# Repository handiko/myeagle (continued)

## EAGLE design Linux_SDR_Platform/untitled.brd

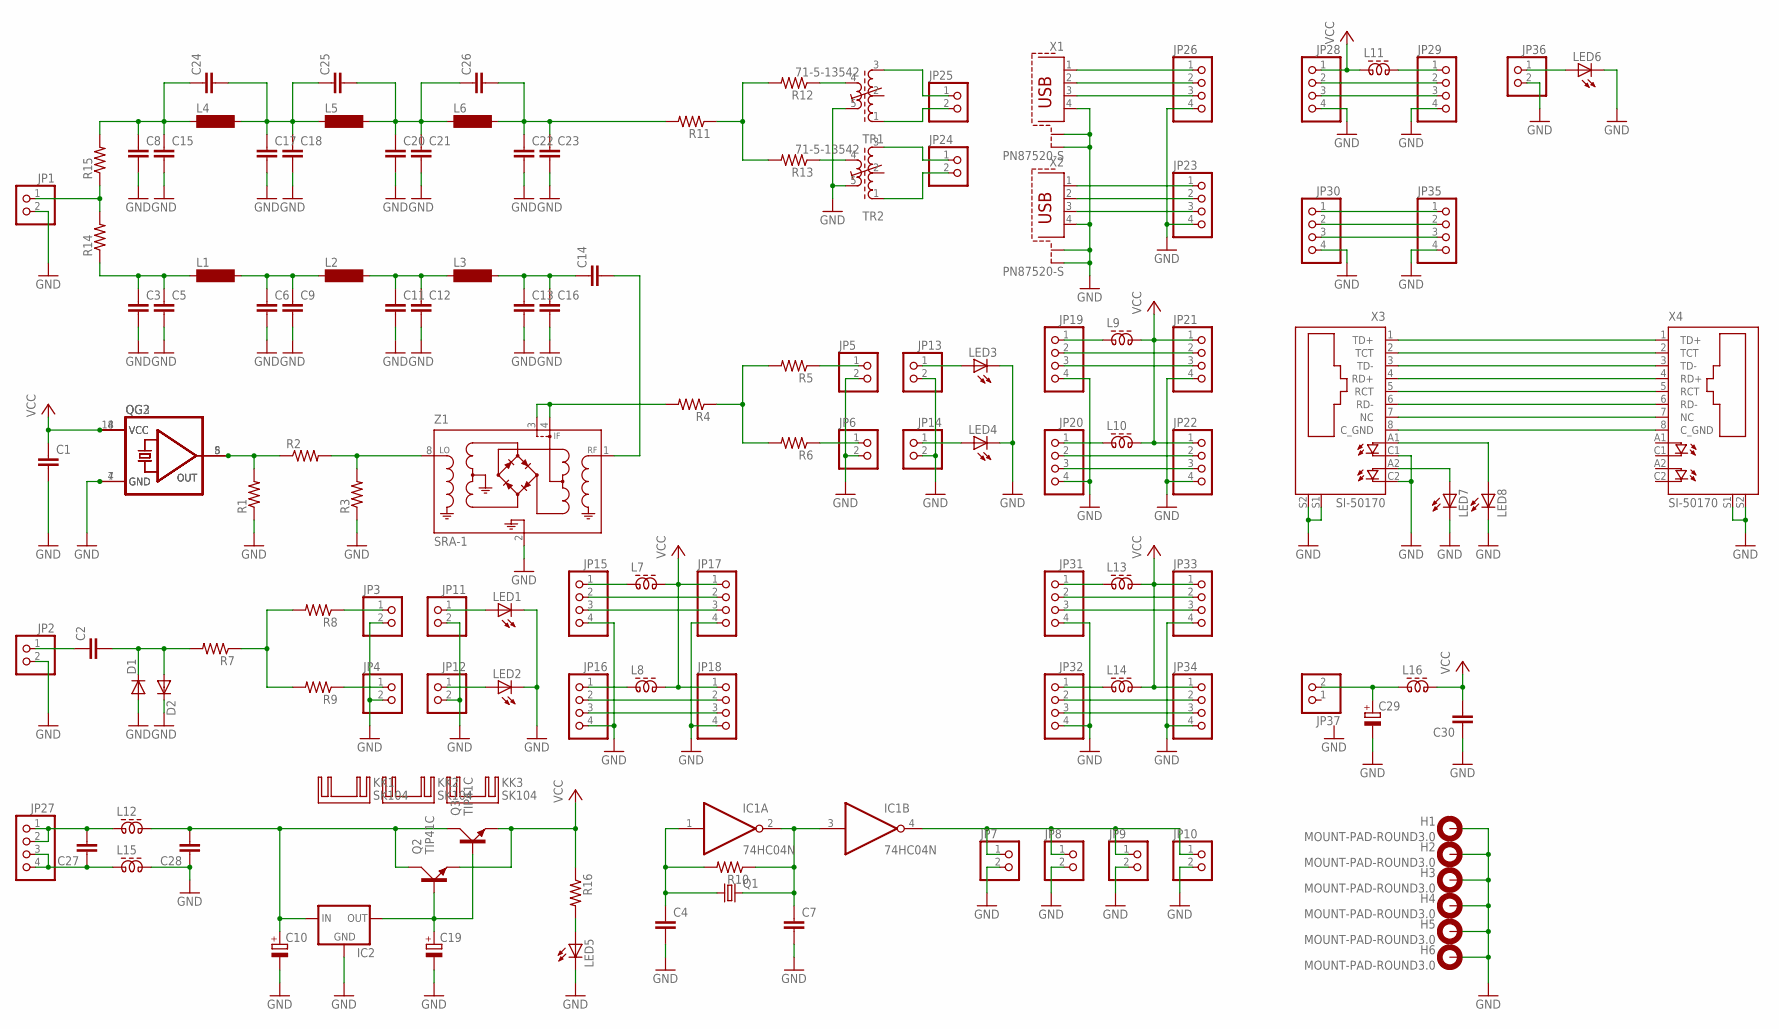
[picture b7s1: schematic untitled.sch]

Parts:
C1, C2, C3, C4, C5, C6, C7, C8, C9, C11, C12, C13, C14, C15, C16, C17, C18, C20, C21, C22, C23, C24, C25, C26, C27, C28, C30: C-EUC1206; C1206
C10, C19, C29: CPOL-EUE2.5-7; E2,5-7
D1, D2: DIODE-DO214AC; DO214AC
H1, H2, H3, H4, H5, H6: MOUNT-PAD-ROUND3.0; 3,0-PAD
IC1: 74HC04N; DIL14
IC2: 78XXS
JP1, JP2, JP3, JP4, JP5, JP6, JP7, JP8, JP9, JP10, JP11, JP12, JP13, JP14, JP24, JP25, JP36, JP37: PINHD-1X2; 1X02
JP15, JP16, JP17, JP18, JP19, JP20, JP21, JP22, JP23, JP26, JP27, JP28, JP29, JP30, JP31, JP32, JP33, JP34, JP35: PINHD-1X4; 1X04
KK1, KK2, KK3: SK104
L1, L2, L3, L4, L5, L6: BS75
L7, L8, L9, L10, L11, L12, L13, L14, L15, L16: ZD60820512; ZD6-2W5
LED1, LED2, LED3, LED4, LED5, LED6, LED7, LED8: LED3MM
Q1: CRYSTALHC49S; HC49/S
Q2, Q3: TIP41C; TO220AV
QG2: QG5460; DIL08S
QG3: QG5860; DIL14S
R1, R2, R3, R4, R5, R6, R7, R8, R9, R10, R11, R12, R13, R14, R15, R16: R-US_M1206; M1206
TR1, TR2: 71-5-13542; 71-5
X1, X2: PN87520-S
X3, X4: SI-50170
Z1: SRA-1; A01

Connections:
GND: C1.2, C3.2, C4.2, C5.2, C6.2, C7.2, C8.2, C9.2, C10.-, C11.2, C12.2, C13.2, C15.2, C16.2, C17.2, C18.2, C19.-, C20.2, C21.2, C22.2, C23.2, C28.1, C29.-, C30.1, D1.A, D2.C, H1.B3,0, H2.B3,0, H3.B3,0, H4.B3,0, H5.B3,0, H6.B3,0, IC1.7 (GND), IC2.GND, JP1.2, JP2.2, JP3.2, JP4.2, JP5.2, JP6.2, JP7.2, JP8.2, JP9.2, JP10.2, JP11.2, JP12.2, JP13.2, JP14.2, JP15.4, JP16.4, JP17.4, JP18.4, JP19.4, JP20.4, JP21.4, JP22.4, JP23.4, JP26.4, JP28.4, JP29.4, JP30.4, JP31.4, JP32.4, JP33.4, JP34.4, JP35.4, JP36.2, L15.2, LED1.K (C), LED2.K (C), LED3.K (C), LED4.K (C), LED5.K (C), LED6.K (C), LED7.K (C), LED8.K (C), QG2.4 (GND), QG3.7 (GND), R1.1, R3.1, TR1.5 (A2), TR2.5 (A2), X1.4, X1.S1, X1.S2, X2.4, X2.S1, X2.S2, X3.C1 (C), X3.C2 (C1), X3.S1, X3.S2, X4.S1, X4.S2, Z1.2 (CASEGROUND), Z1.5 (GND), Z1.6 (GND), Z1.7 (GND)
unnamed: C3.1, C5.1, L1.1, R14.1
unnamed: C6.1, C9.1, L1.2, L2.1
unnamed: JP1.1, R14.2, R15.1
unnamed: C11.1, C12.1, L2.2, L3.1
unnamed: C13.1, C14.1, C16.1, L3.2
unnamed: QG2.5 (OUT), QG3.8 (OUT), R1.2, R2.1
unnamed: R2.2, R3.2, Z1.8 (L)
unnamed: R4.2, Z1.3 (IF), Z1.4 (IF)
unnamed: C14.2, Z1.1 (R)
unnamed: R4.1, R5.2, R6.2
unnamed: C4.1, IC1.1 (I), Q1.1, R10.2
unnamed: C2.1, JP2.1
unnamed: C2.2, D1.C, D2.A, R7.2
unnamed: R7.1, R8.2, R9.2
unnamed: JP3.1, R8.1
unnamed: JP4.1, R9.1
unnamed: JP5.1, R5.1
unnamed: JP6.1, R6.1
unnamed: C7.1, IC1.2 (O), IC1.3 (I), Q1.2, R10.1
unnamed: IC1.4 (O), JP7.1, JP8.1, JP9.1, JP10.1
unnamed: JP11.1, LED1.A
unnamed: JP12.1, LED2.A
unnamed: JP13.1, LED3.A
unnamed: JP14.1, LED4.A
unnamed: JP15.2, JP17.2
unnamed: JP15.3, JP17.3
unnamed: JP16.2, JP18.2
unnamed: JP16.3, JP18.3
unnamed: JP15.1, L7.1
unnamed: JP16.1, L8.1
unnamed: JP19.2, JP21.2
unnamed: JP19.3, JP21.3
unnamed: C8.1, C15.1, C24.1, L4.1, R15.2
unnamed: C17.1, C18.1, C24.2, C25.1, L4.2, L5.1
unnamed: JP20.2, JP22.2
unnamed: C20.1, C21.1, C25.2, C26.1, L5.2, L6.1
unnamed: C22.1, C23.1, C26.2, L6.2, R11.2
unnamed: R13.1, TR2.4 (E2)
unnamed: R11.1, R12.2, R13.2
unnamed: R12.1, TR1.4 (E2)
unnamed: JP25.2, TR1.1 (A1)
unnamed: JP24.1, TR2.3 (E1)
unnamed: JP24.2, TR2.1 (A1)
unnamed: JP25.1, TR1.3 (E1)
unnamed: JP20.3, JP22.3
unnamed: JP19.1, L9.1
unnamed: JP20.1, L10.1
unnamed: JP26.1, X1.1
unnamed: JP26.2, X1.2
unnamed: JP26.3, X1.3
unnamed: JP23.1, X2.1
unnamed: JP23.2, X2.2
unnamed: JP23.3, X2.3
unnamed: C10.+, C28.2, IC2.IN, L12.2, Q2.C, Q3.C
unnamed: C19.+, IC2.OUT, Q2.B, Q3.B
unnamed: JP28.2, JP29.2
unnamed: JP28.3, JP29.3
unnamed: LED5.A, R16.2
unnamed: JP30.2, JP35.2
unnamed: JP31.2, JP33.2
unnamed: JP31.3, JP33.3
unnamed: JP32.2, JP34.2
unnamed: JP32.3, JP34.3
unnamed: JP31.1, L13.1
unnamed: JP32.1, L14.1
unnamed: JP29.1, L11.2
unnamed: JP30.3, JP35.3
unnamed: JP30.1, JP35.1
unnamed: JP36.1, LED6.A
unnamed: X3.1 (TD+), X4.1 (TD+)
unnamed: X3.2 (TCT), X4.2 (TCT)
unnamed: X3.3 (TD-), X4.3 (TD-)
unnamed: X3.4 (RD+), X4.4 (RD+)
unnamed: X3.5 (RCT), X4.5 (RCT)
unnamed: X3.6 (RD-), X4.6 (RD-)
unnamed: X3.7 (NC), X4.7 (NC)
unnamed: X3.8 (C_GND), X4.8 (C_GND)
unnamed: LED7.A, X3.A2 (A1)
unnamed: LED8.A, X3.A1 (A)
unnamed: C27.2, JP27.1, JP27.2, L12.1
unnamed: C27.1, JP27.3, JP27.4, L15.1
unnamed: C29.+, JP37.2, L16.1
VCC: C1.1, C30.2, IC1.14 (VCC), JP17.1, JP18.1, JP21.1, JP22.1, JP28.1, JP33.1, JP34.1, L7.2, L8.2, L9.2, L10.2, L11.1, L13.2, L14.2, L16.2, Q2.E, Q3.E, QG2.8 (VCC), QG3.14 (VCC), R16.1

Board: 2 copper layers, 132 parts (0 on the bottom side), 84 nets, no tracks yet.

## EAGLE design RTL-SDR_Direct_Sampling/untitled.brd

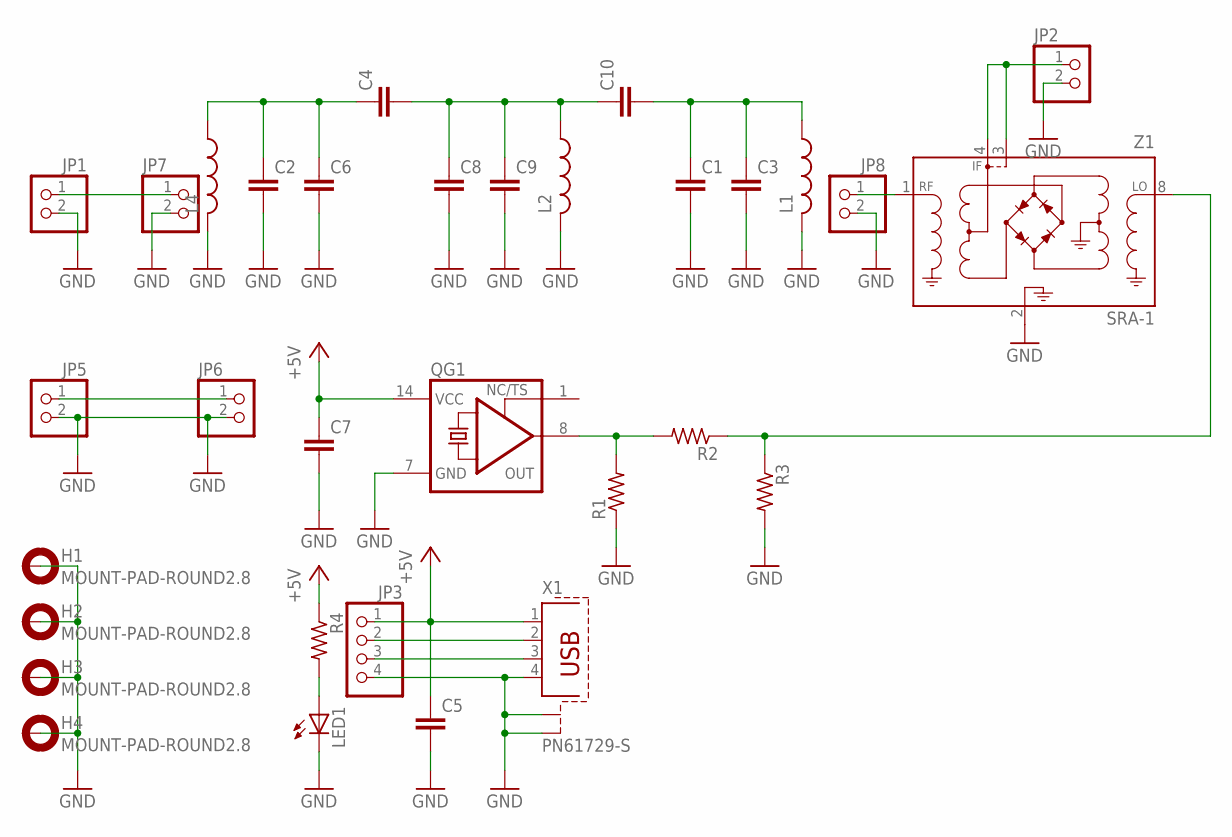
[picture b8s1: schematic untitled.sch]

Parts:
C1, C2, C3, C4, C5, C6, C7, C8, C9, C10: C5/2.5; C5B2.5
H1, H2, H3, H4: MOUNT-PAD-ROUND2.8; 2,8-PAD
JP1, JP2, JP5, JP6, JP7, JP8: PINHD-1X2; 1X02
JP3: PINHD-1X4; 1X04
L1, L2, L4: L-US0207/7; 0207/7
LED1: LED3MM
QG1: XO-14; DIL14S
R1, R2, R3, R4: R-US_0207/7; 0207/7
X1: PN61729-S
Z1: SRA-1; A01

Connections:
+5V: C5.1, C7.1, JP3.1, QG1.14 (VCC), R4.1, X1.1
GND: C1.2, C2.2, C3.2, C5.2, C6.2, C7.2, C8.2, C9.2, JP1.2, JP2.2, JP3.4, JP5.2, JP6.2, JP7.2, JP8.2, L1.2, L2.2, L4.2, LED1.K (C), QG1.7 (GND), R1.1, R3.2, X1.4, X1.S1, X1.S2, Z1.2 (CASEGROUND), Z1.5 (GND), Z1.6 (GND), Z1.7 (GND)
unnamed: JP1.1, JP7.1
unnamed: C2.1, C4.1, C6.1, L4.1
unnamed: C1.1, C3.1, C10.2, L1.1
unnamed: JP8.1, Z1.1 (R)
unnamed: JP2.1, Z1.3 (IF), Z1.4 (IF)
unnamed: QG1.8 (OUT), R1.2, R2.2
unnamed: R2.1, R3.1, Z1.8 (L)
unnamed: LED1.A, R4.2
unnamed: JP3.2, X1.2
unnamed: JP3.3, X1.3
unnamed: C4.2, C8.1, C9.1, C10.1, L2.1
unnamed: JP5.1, JP6.1

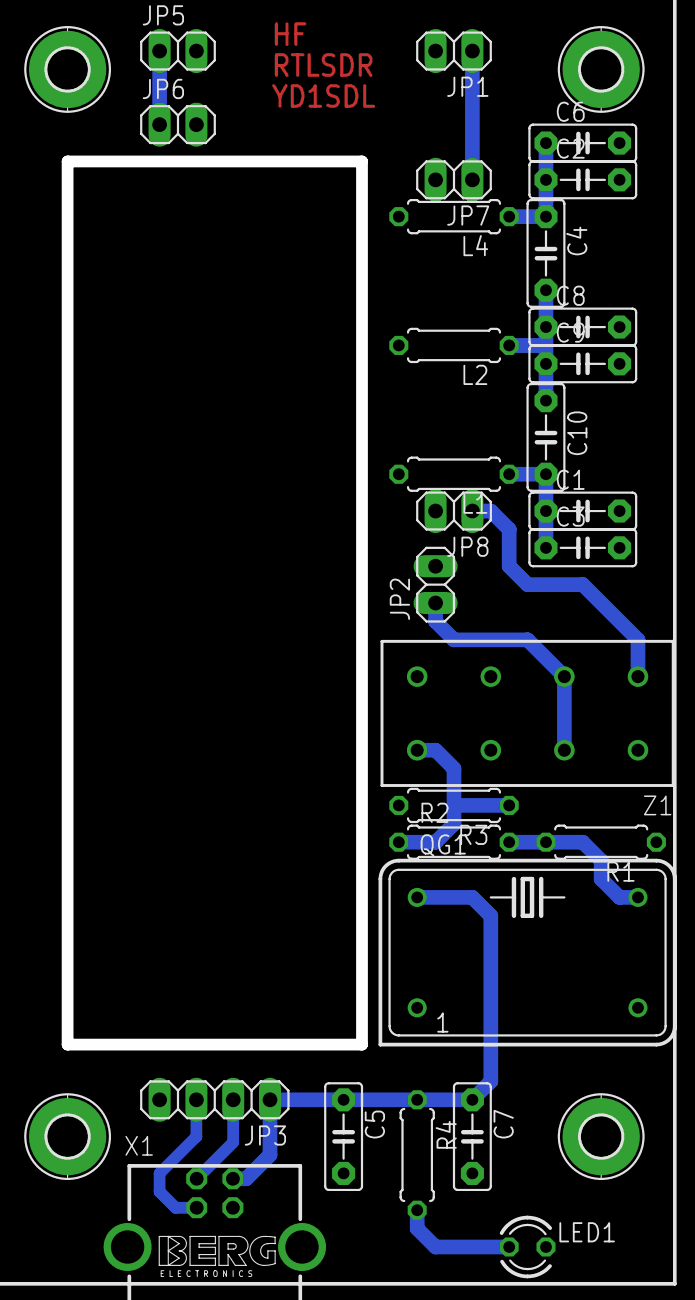
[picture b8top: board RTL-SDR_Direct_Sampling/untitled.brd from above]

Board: 2 copper layers, 32 parts (0 on the bottom side), 14 nets.

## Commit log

2018-10-20 Edit Win10-64
2018-10-22 Changing Output relay configs
2018-10-22 Recommit
2018-10-26 Create LICENSE
2018-10-28 Reconfiguring Relays
2018-10-28 Removing .b# and .s# artifacts
2018-10-28 Adding .gitignore
2018-10-29 Update LICENSE
2018-10-31 Rename LICENSE to Relay Sequencer/LICENSE
2018-11-07 Adding partlist and sch.pdf
2018-11-07 Rename LICENSE to PGA-103- LNA Mod2/LICENSE
2018-11-07 rename folder
2018-11-07 Revalue the components
2019-01-02 Adding libs
2019-01-02 Adding Arduino Libs
2019-01-02 Deleting BelajarCVAVR
2019-01-02 Adding Arduino Shield (Test)
2019-01-02 Adding Dorji Lib
2019-01-03 Adding Arduino-DRA818V-TX
2019-01-03 Adding Arduino-DRA818V-TX Board
2019-01-03 Removing Female header
2019-01-03 Apply SparkFun DRU
2019-01-03 Apply Polygon Pour
2019-01-03 Generate GERBER Files
2019-01-03 Adding GPS Port
2019-01-03 Adding Gerber Files
2019-01-04 Adding Dorji-TX-Shield submodule
2019-01-04 Adding submodule
2019-01-08 Adding pga103 example
2019-01-10 New HI IP3 PGA-103 post LNA BPF
